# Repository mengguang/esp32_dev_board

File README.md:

# esp32_dev_board
esp32 development board
In the Arduino IDE, choose Adafruit ESP32 Feather board.  
The pinout is almost the same as Adafruit ESP32 Feather board except the LED_BUILTIN is 27.

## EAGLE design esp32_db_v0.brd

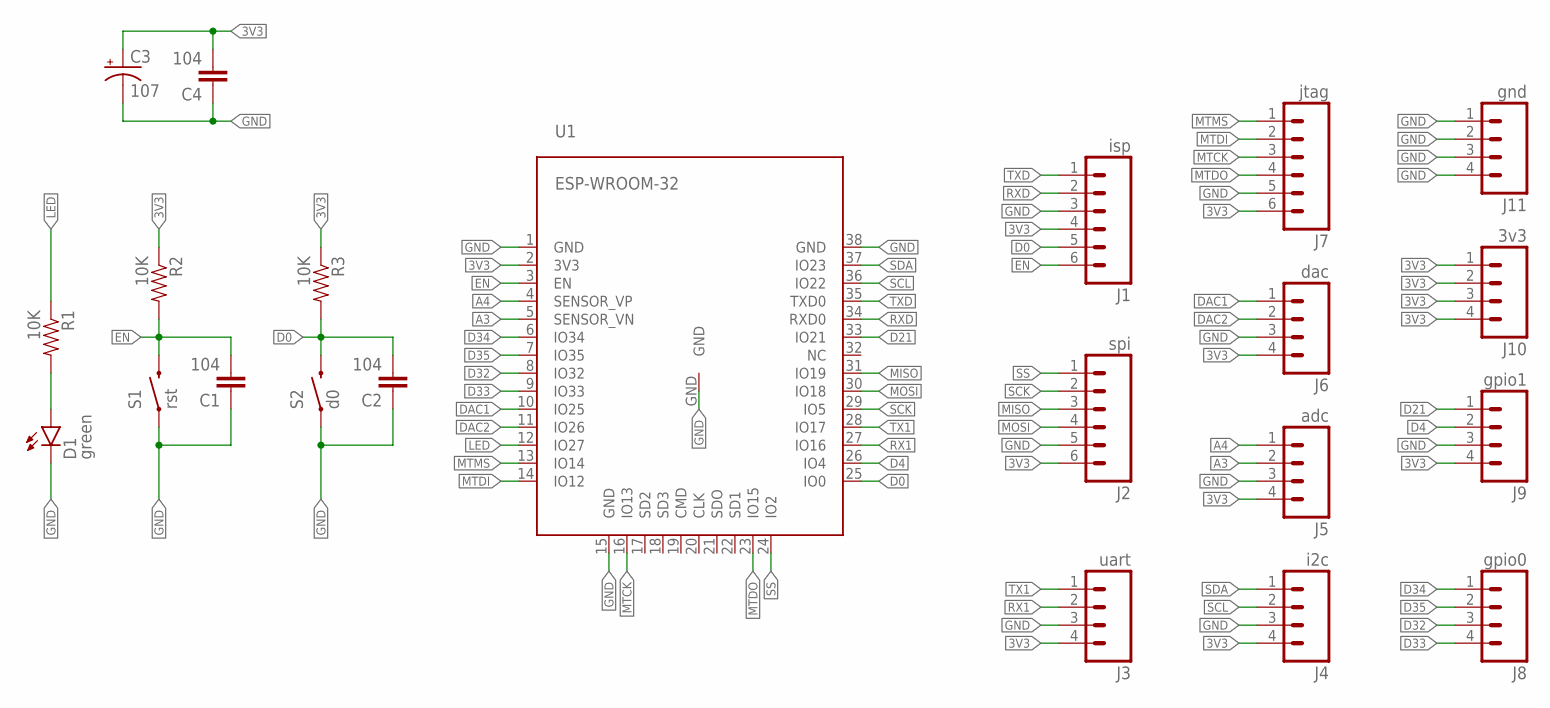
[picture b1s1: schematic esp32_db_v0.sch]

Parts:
C1, C2, C4: 104; 0603-CAP
C3: 107; EIA3528-KIT
D1: green; LED-0603-EASY
J1: isp; 1X06_NO_SILK
J2: spi; 1X06_NO_SILK
J3: uart; 1X04_NO_SILK_ALL_ROUND
J4: i2c; 1X04_NO_SILK_ALL_ROUND
J5: adc; 1X04_NO_SILK_ALL_ROUND
J6: dac; 1X04_NO_SILK_ALL_ROUND
J7: jtag; 1X06_NO_SILK
J8: gpio0; 1X04_NO_SILK_ALL_ROUND
J9: gpio1; 1X04_NO_SILK_ALL_ROUND
J10: 3v3; 1X04_NO_SILK_ALL_ROUND
J11: gnd; 1X04_NO_SILK_ALL_ROUND
R1, R2, R3: 10K; 0603-RES
S1: rst; TACTILE-PTH
S2: d0; TACTILE-PTH
U1: ESP-WROOM-32

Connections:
3V3: C3.A (+), C4.2, J1.4, J2.6, J3.4, J4.4, J5.4, J6.4, J7.6, J9.4, J10.1, J10.2, J10.3, J10.4, R2.1, R3.1, U1.2 (3V3)
A3: J5.2, U1.5 (SENSOR_VN)
A4: J5.1, U1.4 (SENSOR_VP)
D0: C2.2, J1.5, R3.2, S2.3 (2), U1.25 (IO0)
D4: J9.2, U1.26 (IO4)
D21: J9.1, U1.33 (IO21)
D32: J8.3, U1.8 (IO32)
D33: J8.4, U1.9 (IO33)
D34: J8.1, U1.6 (IO34)
D35: J8.2, U1.7 (IO35)
DAC1: J6.1, U1.10 (IO25)
DAC2: J6.2, U1.11 (IO26)
EN: C1.2, J1.6, R2.2, S1.3 (2), U1.3 (EN)
GND: C1.1, C2.1, C3.C (-), C4.1, D1.- (C), J1.3, J2.5, J3.3, J4.3, J5.3, J6.3, J7.5, J9.3, J11.1, J11.2, J11.3, J11.4, S1.1, S2.1, U1.1 (GND), U1.15 (GND), U1.38 (GND), U1.GND
LED: R1.1, U1.12 (IO27)
MISO: J2.3, U1.31 (IO19)
MOSI: J2.4, U1.30 (IO18)
MTCK: J7.3, U1.16 (IO13)
MTDI: J7.2, U1.14 (IO12)
MTDO: J7.4, U1.23 (IO15)
MTMS: J7.1, U1.13 (IO14)
unnamed: D1.+ (A), R1.2
RX1: J3.2, U1.27 (IO16)
RXD: J1.2, U1.34 (RXD0)
SCK: J2.2, U1.29 (IO5)
SCL: J4.2, U1.36 (IO22)
SDA: J4.1, U1.37 (IO23)
SS: J2.1, U1.24 (IO2)
TX1: J3.1, U1.28 (IO17)
TXD: J1.1, U1.35 (TXD0)

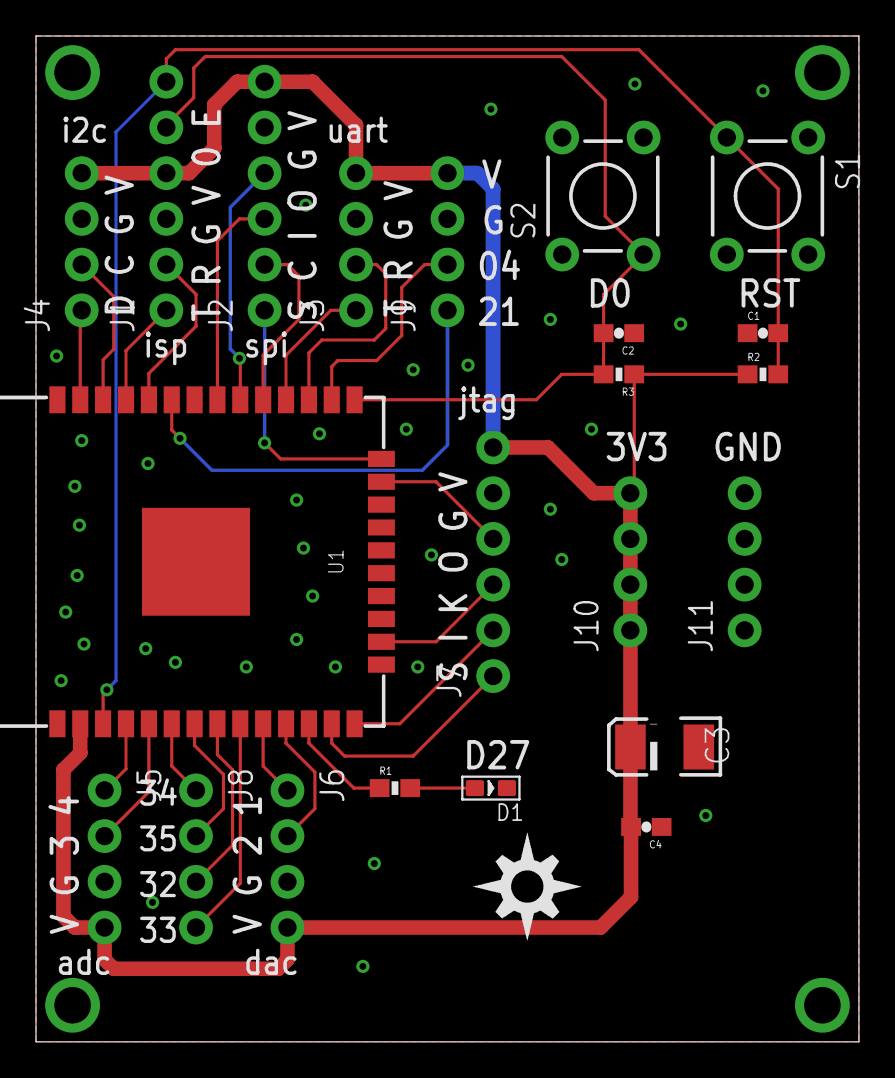
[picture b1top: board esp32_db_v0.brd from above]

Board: 2 copper layers, 45.7 x 55.9 mm, 23 parts (0 on the bottom side), 30 nets.

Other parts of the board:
U$1: DIYNOVA_LOGO

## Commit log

2017-11-02 version 0

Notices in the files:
parts and their libraries:
SparkFun-Connectors: Licensing: Creative Commons ShareAlike 4.0 International - https://creativecommons.org/licenses/by-sa/4.0
